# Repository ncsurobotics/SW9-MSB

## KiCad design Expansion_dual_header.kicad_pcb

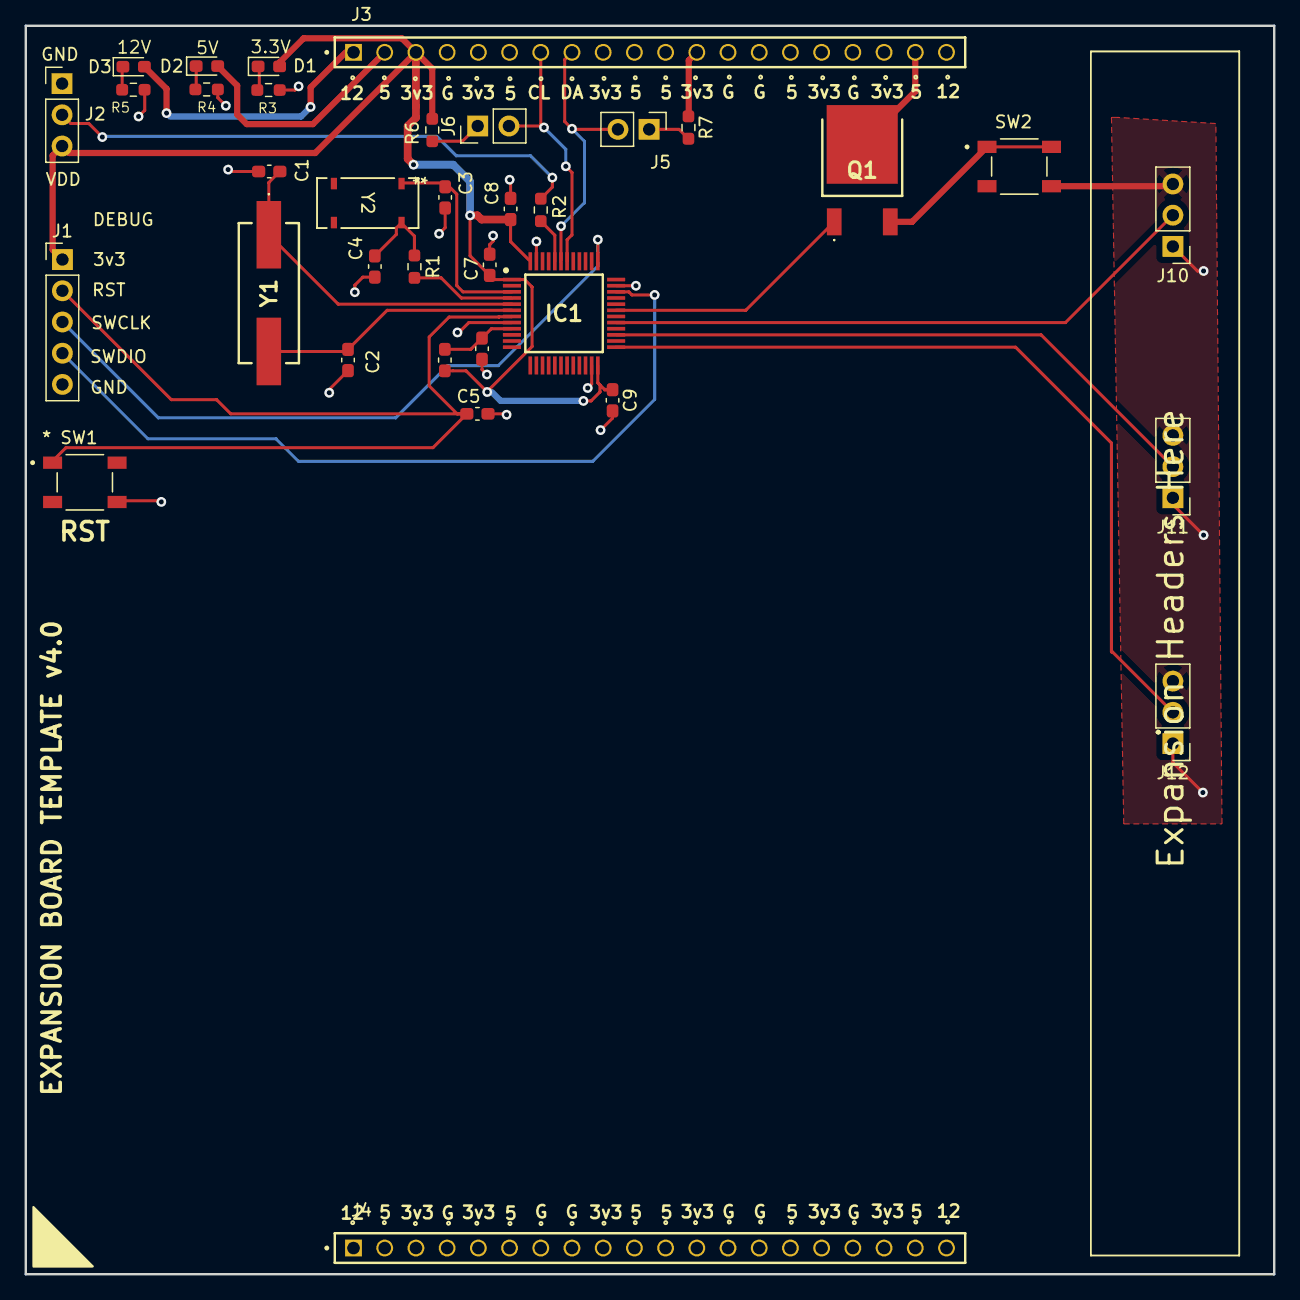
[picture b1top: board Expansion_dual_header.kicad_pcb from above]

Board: 2 copper layers, 101.6 x 101.6 mm, 35 parts (0 on the bottom side), 28 nets.

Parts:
C1, C2: 10p; C_0603_1608Metric_Pad1.08x0.95mm_HandSolder
C3, C4: 15p; C_0603_1608Metric_Pad1.08x0.95mm_HandSolder
C5, C7, C8: 100nF; C_0603_1608Metric_Pad1.08x0.95mm_HandSolder
C6: 1uF; C_0603_1608Metric_Pad1.08x0.95mm_HandSolder
C9: 4.7uF; C_0603_1608Metric_Pad1.08x0.95mm_HandSolder
D1, D2, D3: LED; LED_0603_1608Metric_Pad1.05x0.95mm_HandSolder
FB1: FerriteBead; L_0603_1608Metric_Pad1.05x0.95mm_HandSolder
IC1: STM32L051C6T6; QFP50P900X900X160-48N
J1: Conn_01x05_Pin; PinHeader_1x05_P2.54mm_Vertical
J2, J10, J11, J12: Conn_01x03_Pin; PinHeader_1x03_P2.54mm_Vertical
J3, J4: ESQ-120-14-G-S; SAMTEC_ESQ-120-14-G-S
J5, J6: Conn_01x02_Pin; PinHeader_1x02_P2.54mm_Vertical
Q1: IPD90N04S4-05; IPD90N04S405
R1: 300; R_0603_1608Metric_Pad0.98x0.95mm_HandSolder
R2: 10k; R_0603_1608Metric_Pad0.98x0.95mm_HandSolder
R3: 220; R_0603_1608Metric_Pad0.98x0.95mm_HandSolder
R4: 330; R_0603_1608Metric_Pad0.98x0.95mm_HandSolder
R5: 1k; R_0603_1608Metric_Pad0.98x0.95mm_HandSolder
R6, R7: 4.7k; R_0603_1608Metric_Pad0.98x0.95mm_HandSolder
SW1, SW2: PTS 647 SN50 SMTR2 LFS; SW_PTS_647_SN50_SMTR2_LFS
Y1: 8MHz; 830003151
Y2: 32.768KHZ; X_ABS25_ABR-L

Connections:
5V_Servos: J10.3, J11.3, J12.3, SW2.4
+3V3: C7.1, C8.1, C9.1, D1.2 (A), FB1.1, IC1.1 (VDD_1), IC1.24 (VDD_2), IC1.48 (VDD_3), J1.1, J2.3, J3.03, J3.05, J3.09, J3.12, J3.16, J3.18, J4.03, J4.05, J4.09, J4.12, J4.16, J4.18, R6.1, R7.1
+5V: D2.2 (A), J3.02, J3.06, J3.10, J3.11, J3.15, J3.19, J4.02, J4.06, J4.10, J4.11, J4.15, J4.19, Q1.2 (D)
+12V: D3.2 (A), J3.01, J3.20, J4.01, J4.20
/Microcontroller/PA10: IC1.31 (PA10), Q1.1 (G)
/Microcontroller/PB12: IC1.25 (PB12), J12.2
/SCL: IC1.42 (PB6), J3.07, J6.2
/SDA: IC1.43 (PB7), J3.08, J5.2
/Servos/SERVO1_CTRL: IC1.29 (PA8), J10.2
/Servos/SERVO3_CTRL: IC1.27 (PB14), J11.2
GND: C1.2, C2.2, C3.2, C4.2, C5.2, C6.2, C7.2, C8.2, C9.2, IC1.8 (VSSA), IC1.23 (VSS_1), IC1.35 (VSS_2), IC1.47 (VSS_3), J1.5, J2.1, J3.04, J3.13, J3.14, J3.17, J4.04, J4.07, J4.08, J4.13, J4.14, J4.17, J10.1, J11.1, J12.1, R3.1, R4.1, R5.1, SW1.4
unnamed: C4.1, R1.2, Y2.4 (CRYSTAL)
unnamed: D1.1 (K), R3.2
unnamed: D2.1 (K), R4.2
unnamed: D3.1 (K), R5.2
unnamed: IC1.44 (BOOT0), R2.1
unnamed: C3.1, IC1.3 (PC14-OSC32_IN), Y2.1 (CRYSTAL)
unnamed: IC1.4 (PC15-OSC32_OUT), R1.1
unnamed: C1.1, IC1.5 (PH0-OSC_IN), Y1.1
unnamed: C2.1, IC1.6 (PH1-OSC_OUT), Y1.2
unnamed: J2.2, R2.2
unnamed: J5.1, R7.2
unnamed: J6.1, R6.2
unnamed: Q1.3 (S), SW2.1, SW2.2
RESET: C5.1, IC1.7 (NRST), J1.2, SW1.1
SWCLK/TCK: IC1.37 (PA14), J1.3
SWDIO/TMS: IC1.34 (PA13), J1.4
VDDA: C6.1, FB1.2, IC1.9 (VDDA)

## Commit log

2025-10-30 Adding components to schematics
2025-11-04 Fixed Hierarchy mess
2026-01-22 clarification on servo requirements
2026-01-22 added footprints Servos on PCB
2026-01-29 added MOSFET, and switch for Servos
2026-02-17 add trace lines to PCB
2026-02-17 added picture of plan for mosfet
2026-02-19 added updated pinouts for grabber servo and dropper emagnets
2026-02-19 updated servos with new connectors
2026-02-24 updated servos page with em connections
